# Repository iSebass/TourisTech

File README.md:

# TuristTech

## Introducción

En el contexto de un mundo cada vez más consciente de la importancia de la sostenibilidad y la conservación del medio ambiente, surge un proyecto visionario que busca revolucionar la industria del ecoturismo en Colombia. En este proyecto encontrarás la implementación de una red IoT para monitorear y controlar dispositivos en un ecotel, uniendo la tecnología con la conservación del entorno natural.

## Metodología 

En el marco de este proyecto, la metodología establece las fases fundamentales desde la planificación inicial hasta la culminación del proceso, garantizando una gestión eficaz y coherente en cada etapa. Esta metodología se sustenta en la colaboración interdisciplinaria entre especialistas en tecnología, turismo y conservación, integrando además prácticas ágiles y flexibles para ajustarse a las exigencias y dinámicas del entorno en constante cambio. 

1. **Implementación de Alexa**: La implementación de Alexa marca un avance significativo en el proyecto, al ofrecer una interacción innovadora para los usuarios del ecotel. Este punto de la metodología se enfoca en dos etapas cruciales:
   
    1. **Configuración inicial de Alexa**: Se trata de preparar y conectar los dispositivos necesarios, configurar la aplicación y la cuenta asociada. Esta etapa establece la base tecnológica esencial para la interacción con el asistente de voz. Para la configuración inicial de Alexa, se deben seguir los siguientes pasos:
   
       1. **Descargar la aplicación de Alexa:**
          - Si estás usando un dispositivo Android, descarga la aplicación de Alexa desde [Google Play Store](https://play.google.com/store/apps/details?id=com.amazon.dee.app&pcampaignid=web_share "Google Play Store").
          - Si utilizas un dispositivo Apple, encuentra la aplicación en [App Store](https://apps.apple.com/ni/app/amazon-alexa/id944011620 "App Store").
       
       2. **Vincular o registrar una cuenta de Amazon:**
          - Si aún no tienes una cuenta de Amazon, regístrate.
          - Inicia sesión con tu cuenta de Amazon en la aplicación de Alexa.
       
       3. **Instalar una Skill:**
          - Dentro de la aplicación de Alexa, dirígete a la sección de "Skills" y selecciona "Buscar Skills".
          - Busca la Skill "Ben Hardill - Node-RED" o utiliza este [enlace directo](https://www.amazon.com/Ben-Hardill-Node-RED/dp/B01N0D97FZ) para instalarla.
          - Una vez instalada, sigue las instrucciones para habilitar la Skill y conceder los permisos necesarios para vincular Alexa con Node-RED.
 
   2. **Integración de Alexa con Node-RED**: Aquí, se exploran los pasos para conectar Alexa a Node-RED, una plataforma que facilita la automatización y el control de dispositivos IoT. Se configuran los nodos correspondientes para una comunicación efectiva entre ambos sistemas.

Estas etapas son fundamentales para aprovechar al máximo la implementación de Alexa, mejorando la experiencia del ecoturismo. Una cuidadosa planificación y ejecución en estas áreas sientan las bases para una integración exitosa del asistente de voz en el entorno del ecotel.

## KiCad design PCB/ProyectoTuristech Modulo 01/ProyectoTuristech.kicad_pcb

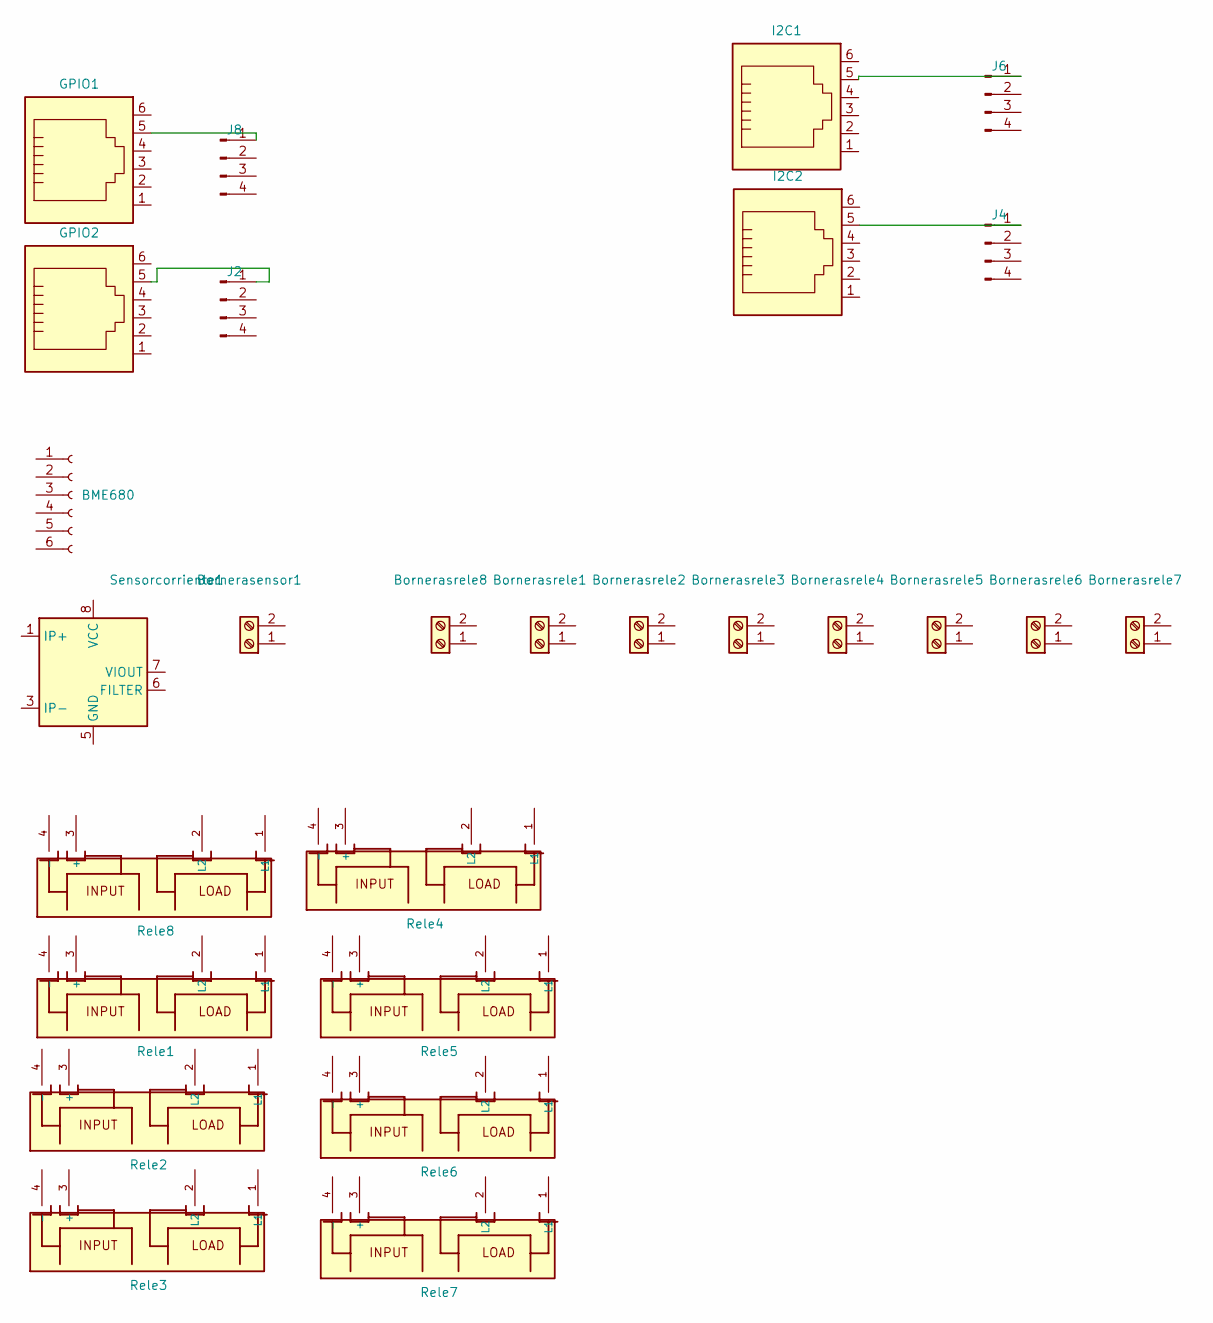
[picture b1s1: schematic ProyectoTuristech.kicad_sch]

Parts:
BME680: Conn_01x06_Socket; PinSocket_1x06_P2.54mm_Vertical
Bornerasensor1: Screw_Terminal_01x02; TerminalBlock_WAGO_236-102_1x02_P5.00mm_45Degree
Bornerasrele1, Bornerasrele2, Bornerasrele3, Bornerasrele4, Bornerasrele5, Bornerasrele6, Bornerasrele7, Bornerasrele8: Screw_Terminal_01x02; TerminalBlock_WAGO_236-102_1x02_P5.00mm_45Degree
GPIO1, GPIO2: 6P6C; RJ25_Wayconn_MJEA-660X1_Horizontal
I2C1, I2C2: 6P6C; RJ25_Wayconn_MJEA-660X1_Horizontal
J2, J4, J6, J8: Conn_01x04_Pin; PinSocket_1x04_P2.54mm_Vertical
Rele1, Rele2, Rele3, Rele4, Rele5, Rele6, Rele7, Rele8: G3MB-202P; RELAY_G3MB-202P
Sensorcorriente1: ACS712xLCTR-30A; SOIC-8_3.9x4.9mm_P1.27mm

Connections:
unnamed: GPIO2.5, J2.1
unnamed: I2C2.5, J4.1
unnamed: I2C1.5, J6.1
unnamed: GPIO1.5, J8.1
unnamed: Sensorcorriente1.1 (IP+), Sensorcorriente1.2 (IP+)
unnamed: Sensorcorriente1.3 (IP-), Sensorcorriente1.4 (IP-)

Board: 2 copper layers, 27 parts (0 on the bottom side), 6 nets, no tracks yet.

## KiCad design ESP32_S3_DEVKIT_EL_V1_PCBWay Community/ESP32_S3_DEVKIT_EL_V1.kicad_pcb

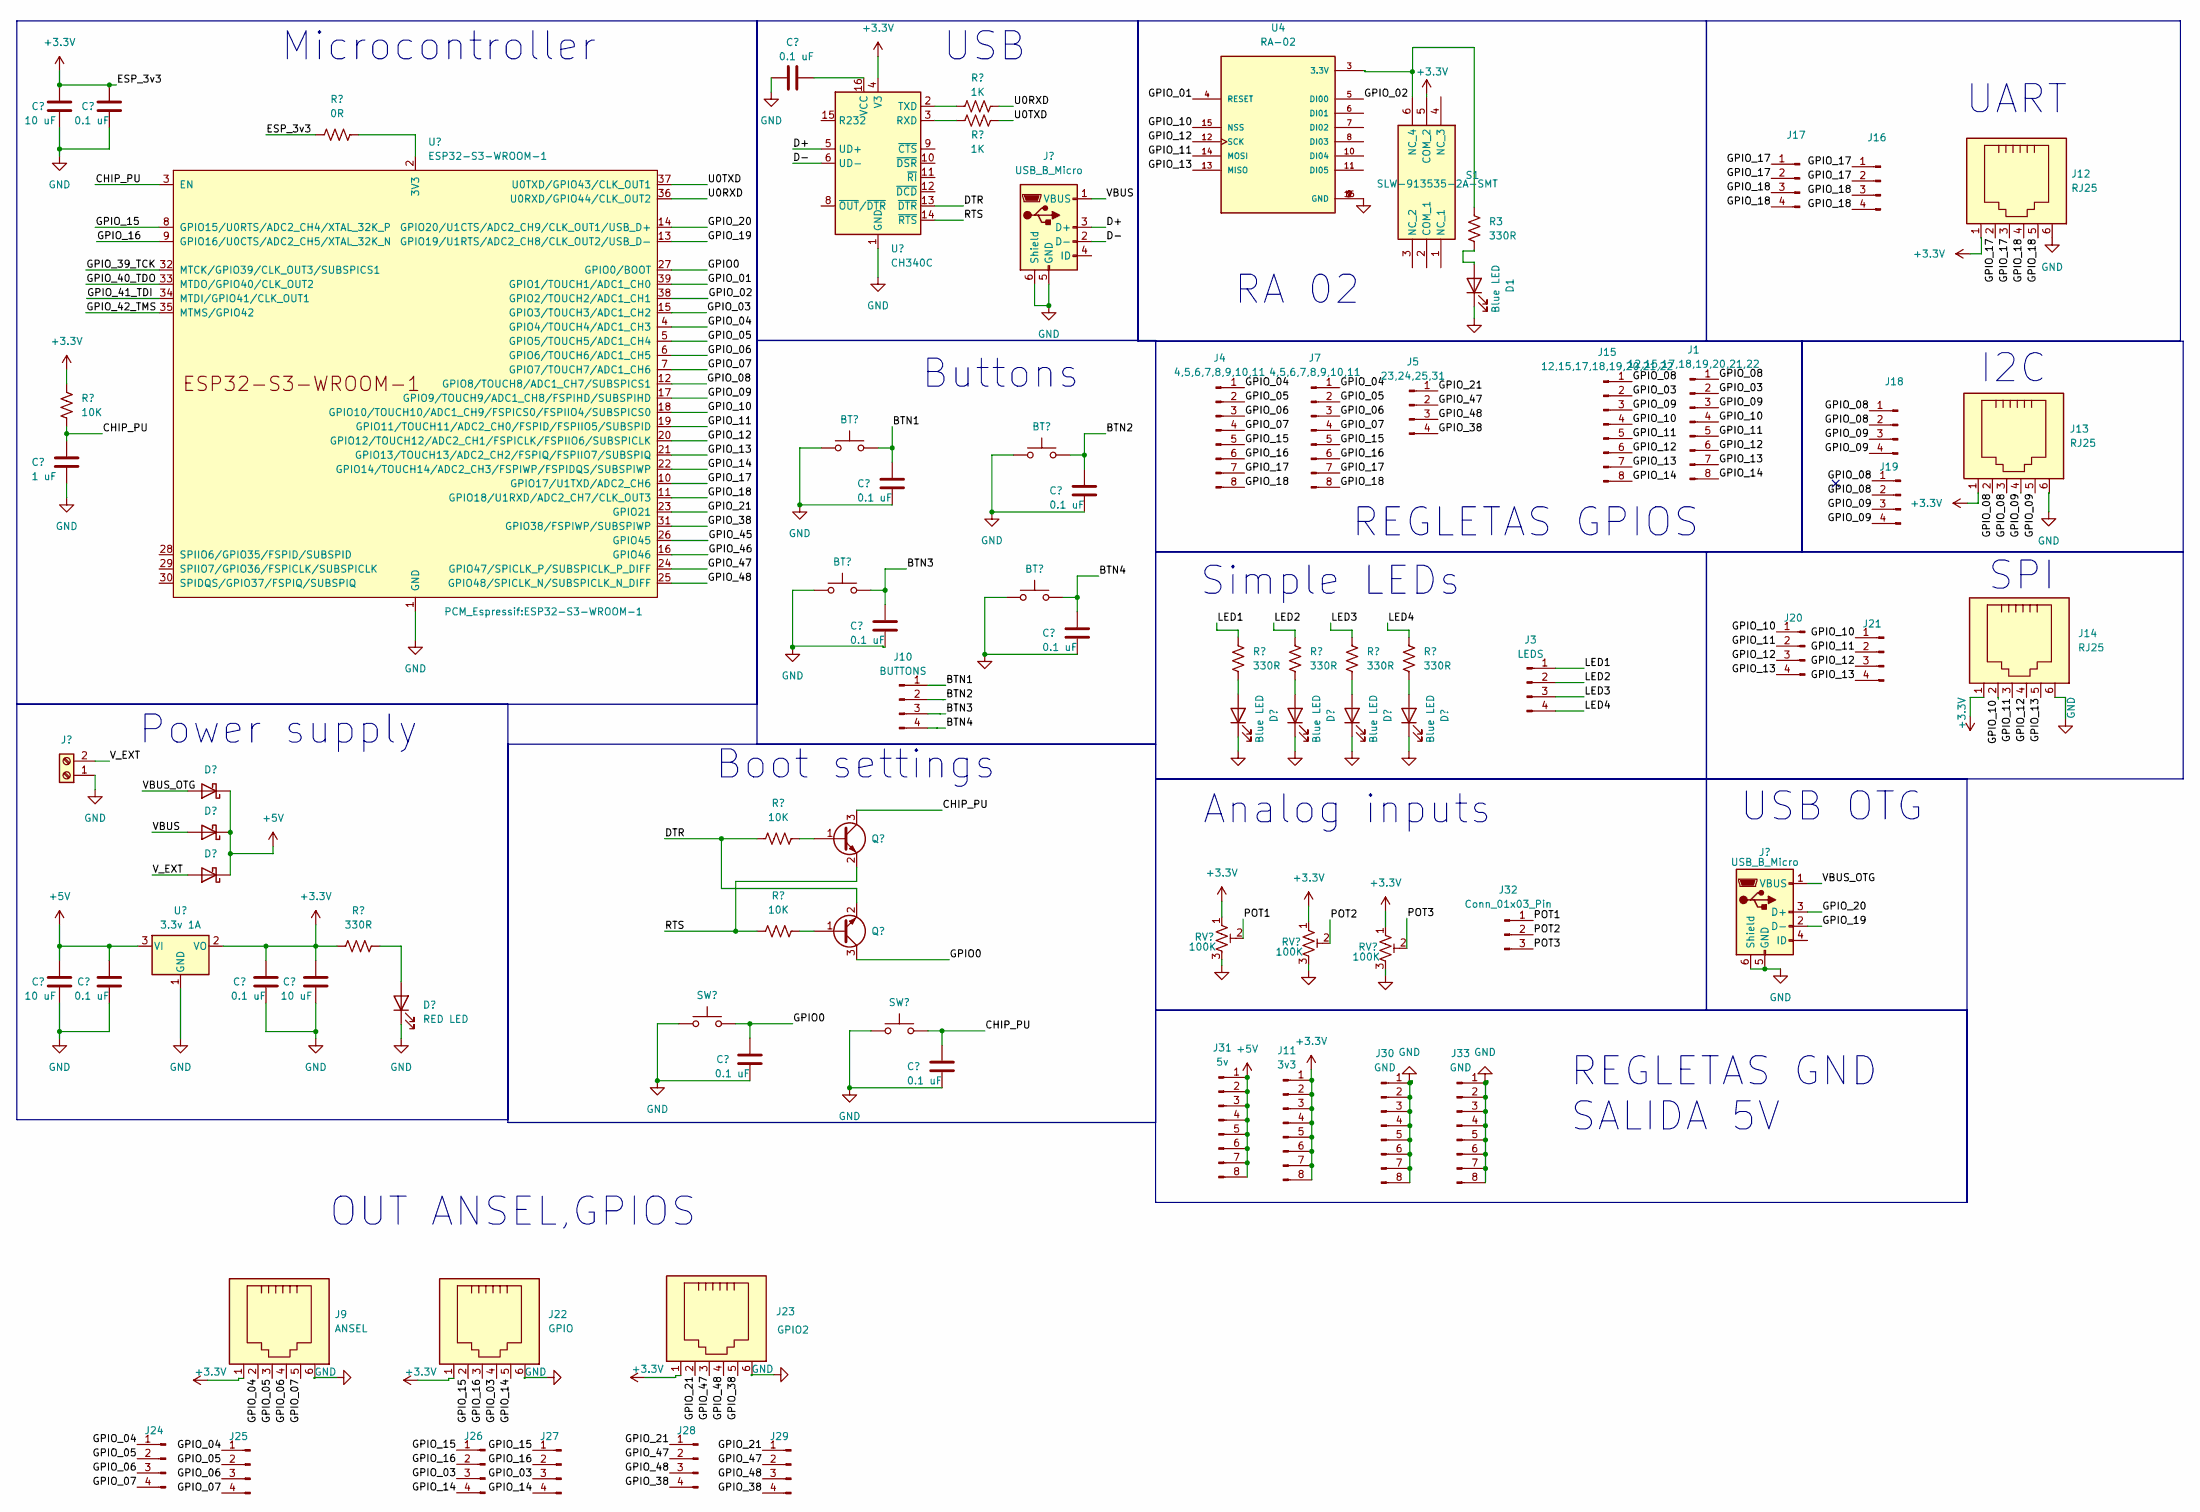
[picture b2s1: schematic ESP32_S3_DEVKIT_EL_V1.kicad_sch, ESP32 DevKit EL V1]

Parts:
BT1, BT2, BT3, BT4: SW_Push; SW_Tactile_SPST_NO_Straight_CK_PTS636Sx25SMTRLFS
C1, C3, C5, C6, C7, C8, C10, C11, C13, C14: 0.1 uF; C_0603_1608Metric_Pad1.08x0.95mm_HandSolder
C2, C9, C12: 10 uF; C_1206_3216Metric_Pad1.33x1.80mm_HandSolder
C4: 1 uF; C_1206_3216Metric_Pad1.33x1.80mm_HandSolder
D1, D7, D8, D9, D10: Blue LED; LED_1206_3216Metric
D11, D12, D13: D_Schottky; D_SMA
D14: RED LED; LED_1206_3216Metric
J1, J15: 12,15,17,18,19,20,21,22; PinHeader_1x08_P2.54mm_Vertical
J2, J8: USB_B_Micro; USB_Micro-B_Molex_47346-0001
J3: LEDS; PinHeader_1x04_P2.54mm_Vertical
J4, J7: 4,5,6,7,8,9,10,11; PinHeader_1x08_P2.54mm_Vertical
J5: 23,24,25,31; PinHeader_1x04_P2.54mm_Vertical
J6: Screw_Terminal_01x02; TerminalBlock_Phoenix_MKDS-1,5-2_1x02_P5.00mm_Horizontal
J9: ANSEL; RJ25_Wayconn_MJEA-660X1_Horizontal
J10: BUTTONS; PinHeader_1x04_P2.54mm_Vertical
J11: 3v3; PinHeader_1x08_P2.54mm_Vertical
J12, J13, J14: RJ25; RJ25_Wayconn_MJEA-660X1_Horizontal
J16, J17, J18, J19, J20, J21, J24, J25, J26, J27, J28, J29: PinHeader_1x04_P2.54mm_Vertical
J22: GPIO; RJ25_Wayconn_MJEA-660X1_Horizontal
J23: GPIO2; RJ25_Wayconn_MJEA-660X1_Horizontal
J30, J33: GND; PinHeader_1x08_P2.54mm_Vertical
J31: 5v; PinHeader_1x08_P2.54mm_Vertical
J32: Conn_01x03_Pin; PinHeader_1x03_P2.54mm_Vertical
Q2, Q3: Q_NPN_BEC; SOT-23-3
R1, R2: 1K; R_1206_3216Metric
R3, R8, R9, R10, R11, R14: 330R; R_1206_3216Metric
R4: 0R; R_1206_3216Metric
R7, R12, R13: 10K; R_1206_3216Metric
RV1, RV2, RV3: 100K; Potentiometer_Bourns_3386P_Vertical
S1: SLW-913535-2A-SMT; SLW9135352ASMT; Mouser Part Number 179-SLW-913535-2ASMT
SW1, SW2: SW_Push; SW_Tactile_SPST_NO_Straight_CK_PTS636Sx25SMTRLFS
U1: CH340C; SOIC-16_3.9x9.9mm_P1.27mm
U2: ESP32-S3-WROOM-1
U3: 3.3v 1A; SOT-223-3_TabPin2
U4: RA-02

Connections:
+3.3V: C2.1, C3.1, C11.1, C12.1, J9.1, J11.1, J11.2, J11.3, J11.4, J11.5, J11.6, J11.7, J11.8, J12.1, J13.1, J14.1, J22.1, J23.1, R4.1, R7.2, R14.1, RV1.1, RV2.1, RV3.1, S1.5 (COM_2), U1.4 (V3), U3.2 (VO); also elsewhere on the board
+5V: C9.1, C10.1, D11.1 (K), D12.1 (K), D13.1 (K), J31.1, J31.2, J31.3, J31.4, J31.5, J31.6, J31.7, J31.8, U3.3 (VI)
/BTN1: BT1.2, C5.1, J10.1
/BTN2: BT2.2, C6.1, J10.2
/BTN3: BT3.2, C7.1, J10.3
/BTN4: BT4.2, C8.1, J10.4
/CHIP_PU: C4.1, C14.1, Q2.3 (C), R7.1, SW2.2, U2.3 (EN); also elsewhere on the board
/D+: J2.3 (D+), U1.5 (UD+)
/D-: J2.2 (D-), U1.6 (UD-)
/DTR: Q3.2 (E), R12.1, U1.13 (~DTR)
/GPIO0: C13.1, Q3.3 (C), SW1.2, U2.27 (GPIO0/BOOT); also elsewhere on the board
/GPIO_01: U2.39 (GPIO1/TOUCH1/ADC1_CH0), U4.4 (RESET)
/GPIO_02: U2.38 (GPIO2/TOUCH2/ADC1_CH1), U4.5 (DI00)
/GPIO_03: J1.2, J15.2, J22.4, J26.3, J27.3, U2.15 (GPIO3/TOUCH3/ADC1_CH2)
/GPIO_04: J4.1, J7.1, J9.2, J24.1, J25.1, U2.4 (GPIO4/TOUCH4/ADC1_CH3)
/GPIO_05: J4.2, J7.2, J9.3, J24.2, J25.2, U2.5 (GPIO5/TOUCH5/ADC1_CH4)
/GPIO_06: J4.3, J7.3, J9.4, J24.3, J25.3, U2.6 (GPIO6/TOUCH6/ADC1_CH5)
/GPIO_07: J4.4, J7.4, J9.5, J24.4, J25.4, U2.7 (GPIO7/TOUCH7/ADC1_CH6)
/GPIO_08: J1.1, J13.2, J13.3, J15.1, J18.1, J18.2, J19.1, J19.2, U2.12 (GPIO8/TOUCH8/ADC1_CH7/SUBSPICS1)
/GPIO_09: J1.3, J13.4, J13.5, J15.3, J18.3, J18.4, J19.3, J19.4, U2.17 (GPIO9/TOUCH9/ADC1_CH8/FSPIHD/SUBSPIHD)
/GPIO_10: J1.4, J14.2, J15.4, J20.1, J21.1, U2.18 (GPIO10/TOUCH10/ADC1_CH9/FSPICS0/FSPIIO4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), U4.15 (NSS)
/GPIO_11: J1.5, J14.3, J15.5, J20.2, J21.2, U2.19 (GPIO11/TOUCH11/ADC2_CH0/FSPID/FSPIIO5/S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), U4.14 (MOSI)
/GPIO_12: J1.6, J14.4, J15.6, J20.3, J21.3, U2.20 (GPIO12/TOUCH12/ADC2_CH1/FSPICLK/FSPIIO6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), U4.12 (SCK)
/GPIO_13: J1.7, J14.5, J15.7, J20.4, J21.4, U2.21 (GPIO13/TOUCH13/ADC2_CH2/FSPIQ/FSPIIO7/S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), U4.13 (MISO)
/GPIO_14: J1.8, J15.8, J22.5, J26.4, J27.4, U2.22 (GPIO14/TOUCH14/ADC2_CH3/FSPIWP/FSPIDQS/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)
/GPIO_15: J4.5, J7.5, J22.2, J26.1, J27.1, U2.8 (GPIO15/U0RTS/ADC2_CH4/XTAL_32K_P)
/GPIO_16: J4.6, J7.6, J22.3, J26.2, J27.2, U2.9 (GPIO16/U0CTS/ADC2_CH5/XTAL_32K_N)
/GPIO_17: J4.7, J7.7, J12.2, J12.3, J16.1, J16.2, J17.1, J17.2, U2.10 (GPIO17/U1TXD/ADC2_CH6)
/GPIO_18: J4.8, J7.8, J12.4, J12.5, J16.3, J16.4, J17.3, J17.4, U2.11 (GPIO18/U1RXD/ADC2_CH7/CLK_OUT3)
/GPIO_19: J8.2 (D-), U2.13 (GPIO19/U1RTS/ADC2_CH8/CLK_OUT2/USB_D-)
/GPIO_20: J8.3 (D+), U2.14 (GPIO20/U1CTS/ADC2_CH9/CLK_OUT1/USB_D+)
/GPIO_21: J5.1, J23.2, J28.1, J29.1, U2.23 (GPIO21)
/GPIO_38: J5.4, J23.5, J28.4, J29.4, U2.31 (GPIO38/FSPIWP/SUBSPIWP)
/GPIO_39_TCK: U2.32 (MTCK/GPIO39/CLK_OUT3/SUBSPICS1)
/GPIO_40_TDO: U2.33 (MTDO/GPIO40/CLK_OUT2)
/GPIO_41_TDI: U2.34 (MTDI/GPIO41/CLK_OUT1)
/GPIO_42_TMS: U2.35 (MTMS/GPIO42)
/GPIO_45: U2.26 (GPIO45)
/GPIO_46: U2.16 (GPIO46)
/GPIO_47: J5.2, J23.3, J28.2, J29.2, U2.24 (GPIO47/SPICLK_P/SUBSPICLK_P_DIFF)
/GPIO_48: J5.3, J23.4, J28.3, J29.3, U2.25 (GPIO48/SPICLK_N/SUBSPICLK_N_DIFF)
/LED1: J3.1, R8.2
/LED2: J3.2, R9.2
/LED3: J3.3, R10.2
/LED4: J3.4, R11.2
/POT1: J32.1, RV1.2
/POT2: J32.2, RV2.2
/POT3: J32.3, RV3.2
/RTS: Q2.2 (E), R13.1, U1.14 (~RTS)
/U0RXD: R1.2, U2.36 (U0RXD/GPIO44/CLK_OUT2)
/U0TXD: R2.2, U2.37 (U0TXD/GPIO43/CLK_OUT1)
/VBUS: D12.2 (A), J2.1 (VBUS)
/VBUS_OTG: D11.2 (A), J8.1 (VBUS)
/V_EXT: D13.2 (A), J6.2
GND: BT1.1, BT2.1, BT3.1, BT4.1, C1.2, C2.2, C3.2, C4.2, C5.2, C6.2, C7.2, C8.2, C9.2, C10.2, C11.2, C12.2, C13.2, C14.2, D1.1 (K), D7.1 (K), D8.1 (K), D9.1 (K), D10.1 (K), D14.1 (K), J2.5 (GND), J2.6 (Shield), J6.1, J8.5 (GND), J8.6 (Shield), J9.6, J12.6, J13.6, J14.6, J22.6, J23.6, J30.1, J30.2, J30.3, J30.4, J30.5, J30.6, J30.7, J30.8, J33.1, J33.2, J33.3, J33.4, J33.5, J33.6, J33.7, J33.8, RV1.3, RV2.3, RV3.3, SW1.1, SW2.1, U1.1 (GND), U2.1 (GND), U2.40 (GND), U2.41 (GND), U3.1 (GND), U4.1 (GND), U4.2 (GND), U4.9 (GND), U4.16 (GND); also elsewhere on the board
unnamed: D1.2 (A), R3.1
unnamed 56: D7.2 (A), R8.1; also elsewhere on the board
unnamed 57: D8.2 (A), R9.1; also elsewhere on the board
unnamed 58: D9.2 (A), R10.1; also elsewhere on the board
unnamed 59: D10.2 (A), R11.1; also elsewhere on the board
unnamed: D14.2 (A), R14.2
unnamed: Q2.1 (B), R12.2
unnamed: Q3.1 (B), R13.2
unnamed 63: R3.2, S1.6 (NC_4), U4.3 (3.3V); also elsewhere on the board
unnamed: R2.1, U1.3 (RXD)
unnamed: R1.1, U1.2 (TXD)
unnamed: C1.1, U1.16 (VCC)
unnamed: R4.2, U2.2 (3V3)

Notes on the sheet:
Buttons
I2C
RA 02
SPI
REGLETAS GPIOS
Power supply
USB OTG
Simple LEDs
USB
UART
Microcontroller
REGLETAS GND SALIDA 5V
OUT ANSEL,GPIOS
Boot settings
Analog inputs

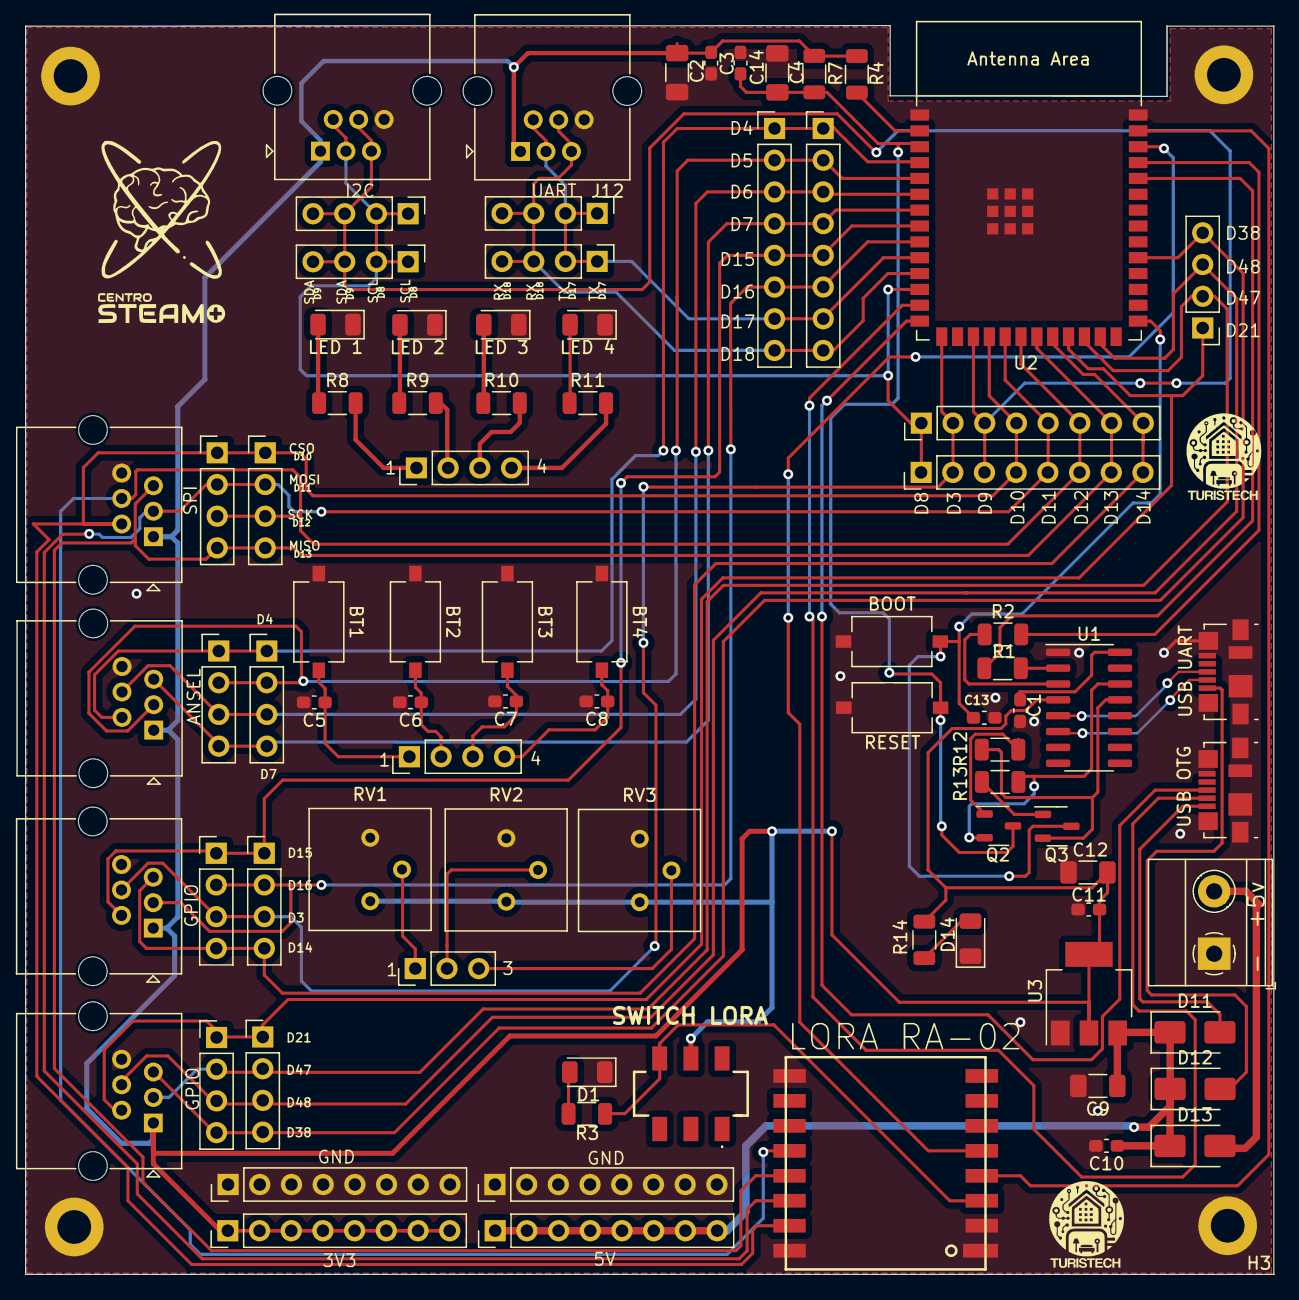
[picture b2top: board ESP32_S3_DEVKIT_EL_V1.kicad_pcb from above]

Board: 2 copper layers, 100.0 x 100.0 mm, 85 parts (0 on the bottom side), 62 nets.

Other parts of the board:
BOOT: SW_Push; SW_Tactile_SPST_NO_Straight_CK_PTS636Sx25SMTRLFS
H3: MountingHole_2.7mm_M2.5_DIN965_Pad
LED 1, LED 2, LED 3, LED 4: Blue LED; LED_1206_3216Metric
RESET: SW_Push; SW_Tactile_SPST_NO_Straight_CK_PTS636Sx25SMTRLFS
SWITCH LORA: SLW-913535-2A-SMT; SLW9135352ASMT

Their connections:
+3.3V: SWITCH LORA.5 (COM_2); also elsewhere on the board
/CHIP_PU: RESET.2; also elsewhere on the board
/GPIO0: BOOT.2; also elsewhere on the board
GND: BOOT.1, H3.3, LED 1.1 (K), LED 2.1 (K), LED 3.1 (K), LED 4.1 (K), RESET.1; also elsewhere on the board
unnamed 56: LED 1.2 (A); also elsewhere on the board
unnamed 57: LED 2.2 (A); also elsewhere on the board
unnamed 58: LED 3.2 (A); also elsewhere on the board
unnamed 59: LED 4.2 (A); also elsewhere on the board
unnamed 63: SWITCH LORA.6 (NC_4); also elsewhere on the board

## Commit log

2023-08-20 Se agregan primeros codigos del proyecto
2023-08-22 Se agregan archivos de PCB y codigos de Python FUncionando@
2023-08-22 Se actualiza Boot.py
2023-08-22 Se actualiza codigo con Credenciales de Ubidots Julian
2024-02-19 README.md
2024-03-20 PCB - PLACA MADRE
2024-03-20 PlacaOtraVez
2024-04-03 Ultima PCB
    PCB Final
2024-04-06 Nueva version del esquematico de la placa
    La unica modificacion que hice fue organizar un poco mejor el esquematico, osea el archivo .kicad_sch
2024-04-06 Version de frabricacion 01
2024-04-12 Se agregan modelos 3D
2024-04-12 Se agrega PCB del modulo 01
